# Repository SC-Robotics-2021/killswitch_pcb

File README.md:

# Killswitch PCB
Hard and soft stop pcb for the rover. 
The hard stop cuts power for all subsystems. The soft stop also cuts power but it leaves computing power on. 
The PCB controls the energization of the Electrical (computing power), Arm, and Drive relay's coil.

The design of the PCB is recorded in [osiris_meta #51](https://github.com/SC-Robotics-2021/osiris_meta/issues/51).

## Materials for the PCB
- General purpose diodes
- Screw terminals
- ~~48V-coil Relays~~ 12V-coil Relays
- ~~500 ohm resistor~~ no resistor for relay's coil
- Coin cell battery for OR gate
- 10k pull down resistors

## Cool photo of first assembly

<sup>(02.22.2022)</sup>

## 02/22/2022 Testing PCB
During testing ([osiris_meta #67](https://github.com/SC-Robotics-2021/osiris_meta/issues/67)), 
the resistors for the coil (500 ohm, 1/4 W) smoked. Using a higher resistance (6k ohm) fixed the smoking issue, 
but the resistor got warm. The problem can be fixed using higher wattage resistors, but 
I didn't have time to get them.
The resistors were used to limit the current going to the coils as a safety precaution, but the current drawn from 
the coil is already small, so I opted to not use a resistor and short the endings on the PCB (soldered a wire 
instead of a resistor). 

PCB works as intended without the coil resistors! The 48-V coil relay warms after less than one minute, I read online that
this is a normal behaviour of relays, but one minute is too little time.   

## Integration in the rover
This is the schematic of how the killswitch was connected to the protection layers already in the rover.
Notice that the circuit breaker goes before the relay.

## 05/18/2022 More testing
The metal switch contacts of the relays melted together from overheat. 

I had connected the 48V battery into the system, and not the 12V battery. After 5 minutes, I noticed the relays were hot. 
With the design of the killswitch, not having one battery (48 or 12) should not have been an issue. After troubleshooting, 
I concluded it was the relays and not the design of the PCB. Note that since the beginning, the relays were not reliable. 
The vendor didn't provide any datasheet and the build of the relay was not very professional. (The relays were bought from a 
third party in Walmart during the time when the team was discouraged from buying from Amazon).

I replaced the unreliable 48V coil relay with 12V ones that I found on Amazon. 

## Re-implementation in the rover

## Summary of changes

- No longer using the Arm relay
- No resistor for coil, wire instead
- New relay's coil voltage is 12V 
- The same 12V battery energizes all relays' coil. Relays provide isolation between the control signal and the switch contact
 
_The changes were not made to the PCB itself due to lack of time._ 

A summary of all changes is in the picture:

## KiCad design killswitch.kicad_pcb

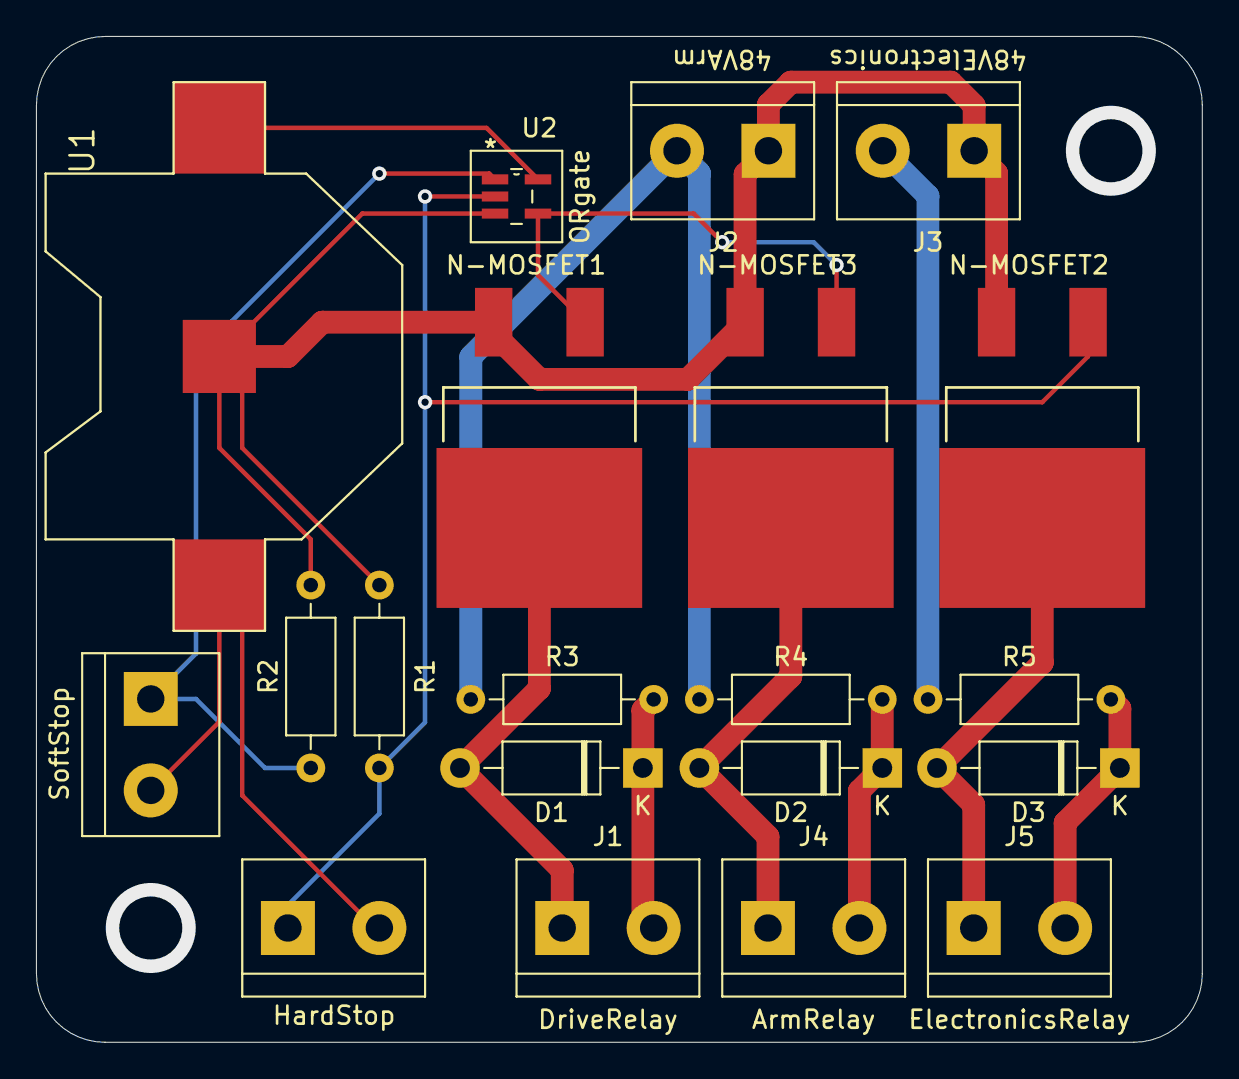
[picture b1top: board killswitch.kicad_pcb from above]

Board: 2 copper layers, 64.8 x 55.9 mm, 20 parts (0 on the bottom side), 13 nets.

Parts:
D1, D2, D3: 1N4001; D_DO-41_SOD81_P10.16mm_Horizontal
HardStop: HS; TerminalBlock_bornier-2_P5.08mm
J1, J2, J3, J4, J5: Screw_Terminal_01x02; TerminalBlock_bornier-2_P5.08mm
N-MOSFET1, N-MOSFET2, N-MOSFET3: IRFS3806TRLPBF; NChan_MOSFET_IPB026N06NATMA1
R1, R2: 10K; R_Axial_DIN0207_L6.3mm_D2.5mm_P10.16mm_Horizontal
R3, R4, R5: 500; R_Axial_DIN0207_L6.3mm_D2.5mm_P10.16mm_Horizontal
SoftStop: SS; TerminalBlock_bornier-2_P5.08mm
U1: CR2032_Holder; CR2032_Holder_SMD
U2: ORgate; SN74AUP1G32DBVT_ORgate

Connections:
3V: HardStop.1, SoftStop.1, U1.+$1, U1.+$2, U2.5
48V_electronics: J3.1, R5.1
+48V: J2.1, R3.1, R4.1
GND: J2.2, J3.2, N-MOSFET1.3, N-MOSFET2.3, N-MOSFET3.3, R1.2, R2.2, U1.-, U2.3
HS: HardStop.2, N-MOSFET2.1, R1.1, U2.2
ORout: N-MOSFET1.1, N-MOSFET3.1, U2.4
SS: R2.1, SoftStop.2, U2.1
outRelay1: D1.1, J1.2, R3.2
outRelay2: D2.1, J4.2, R4.2
outRelay3: D3.1, J5.2, R5.2
toRelay1: D1.2, J1.1, N-MOSFET1.2
toRelay2: D2.2, J4.1, N-MOSFET3.2
toRelay3: D3.2, J5.1, N-MOSFET2.2

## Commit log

2022-05-29 added gitignore

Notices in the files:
parts and their libraries:
Copyright 2021 Accelerated Designs. All rights reserved.
